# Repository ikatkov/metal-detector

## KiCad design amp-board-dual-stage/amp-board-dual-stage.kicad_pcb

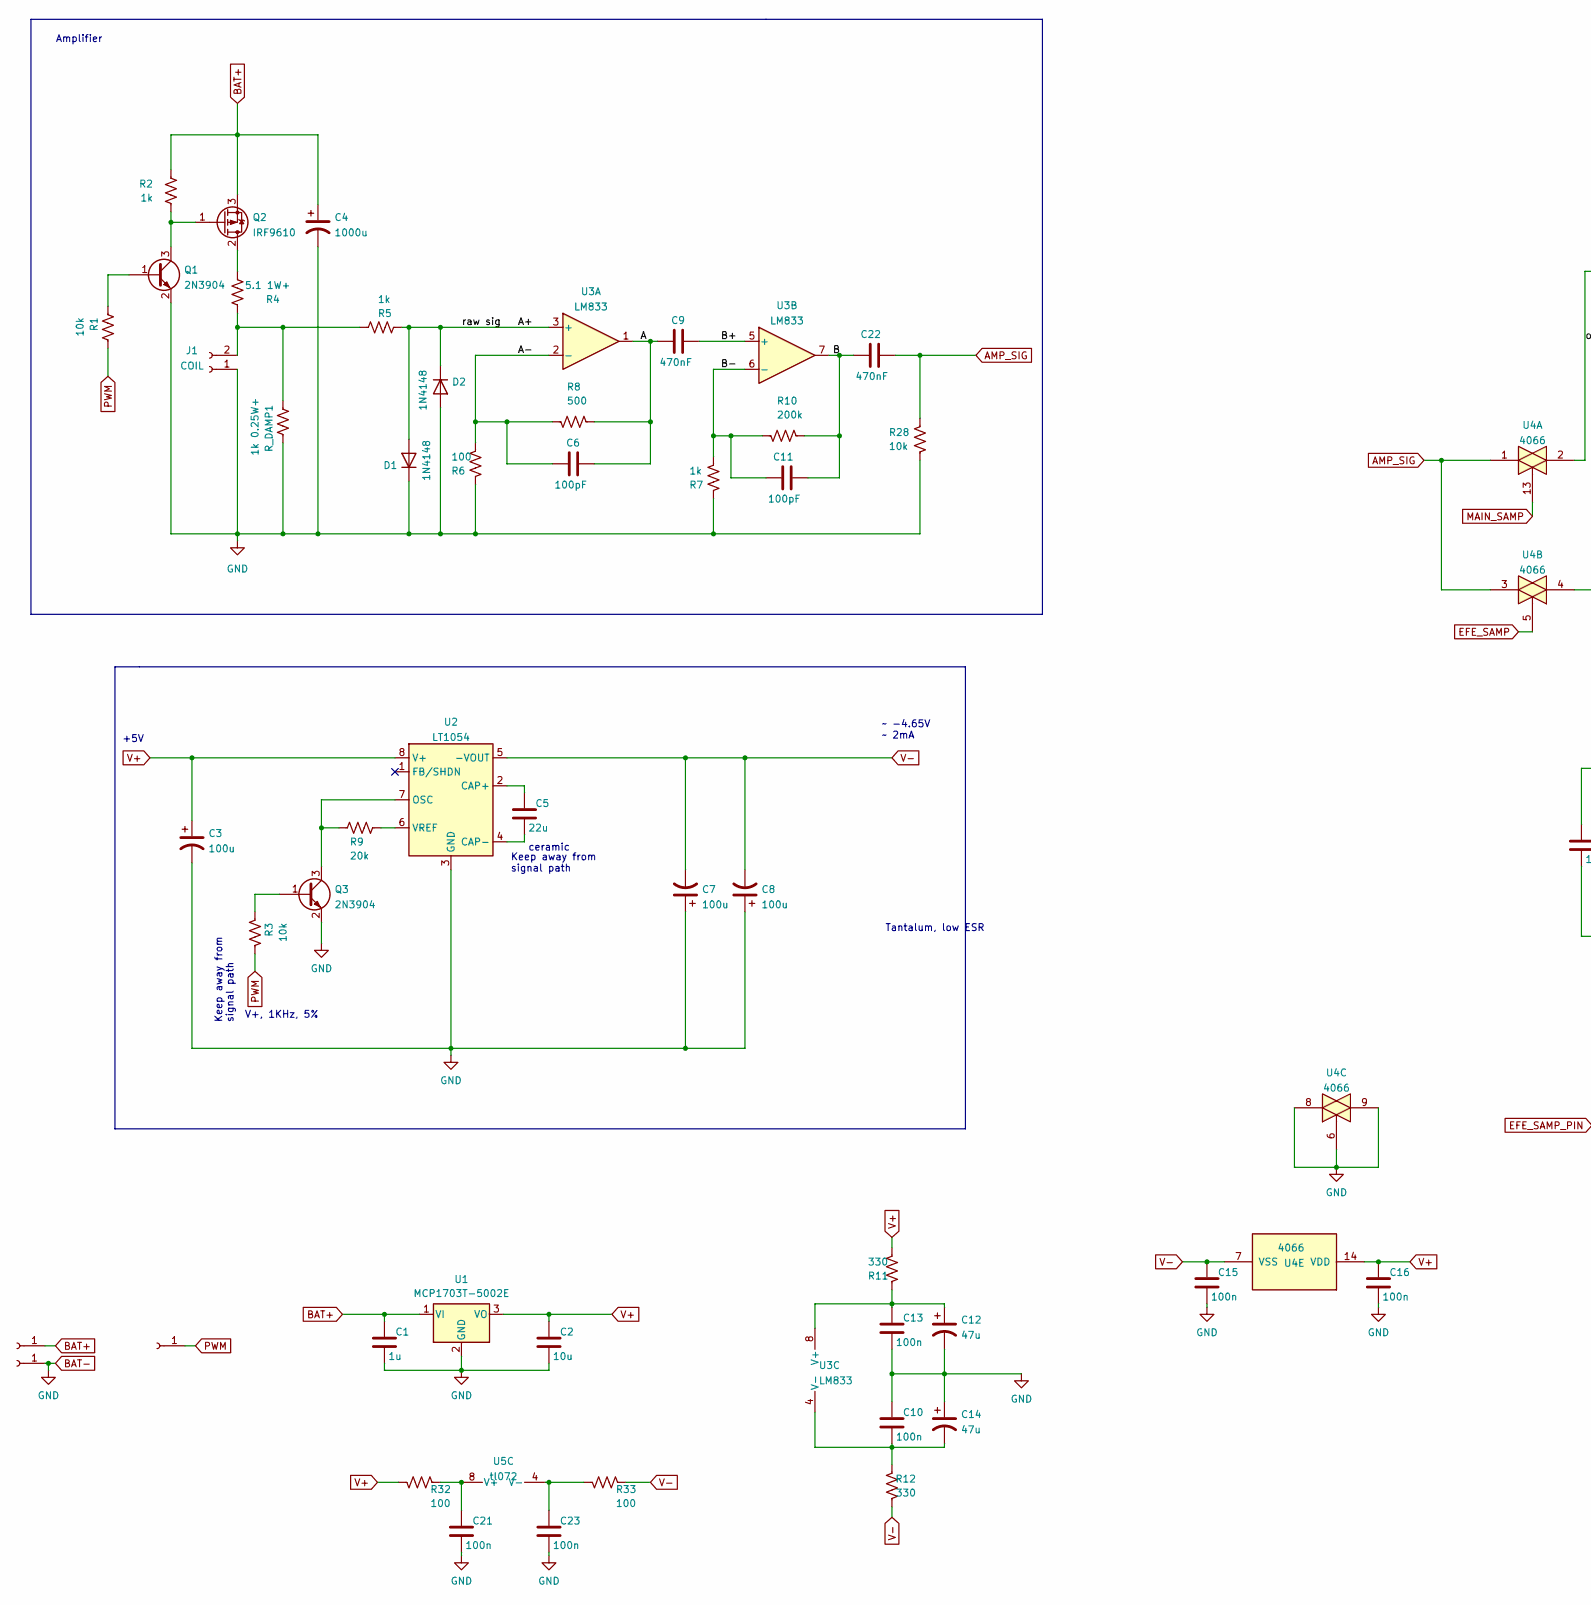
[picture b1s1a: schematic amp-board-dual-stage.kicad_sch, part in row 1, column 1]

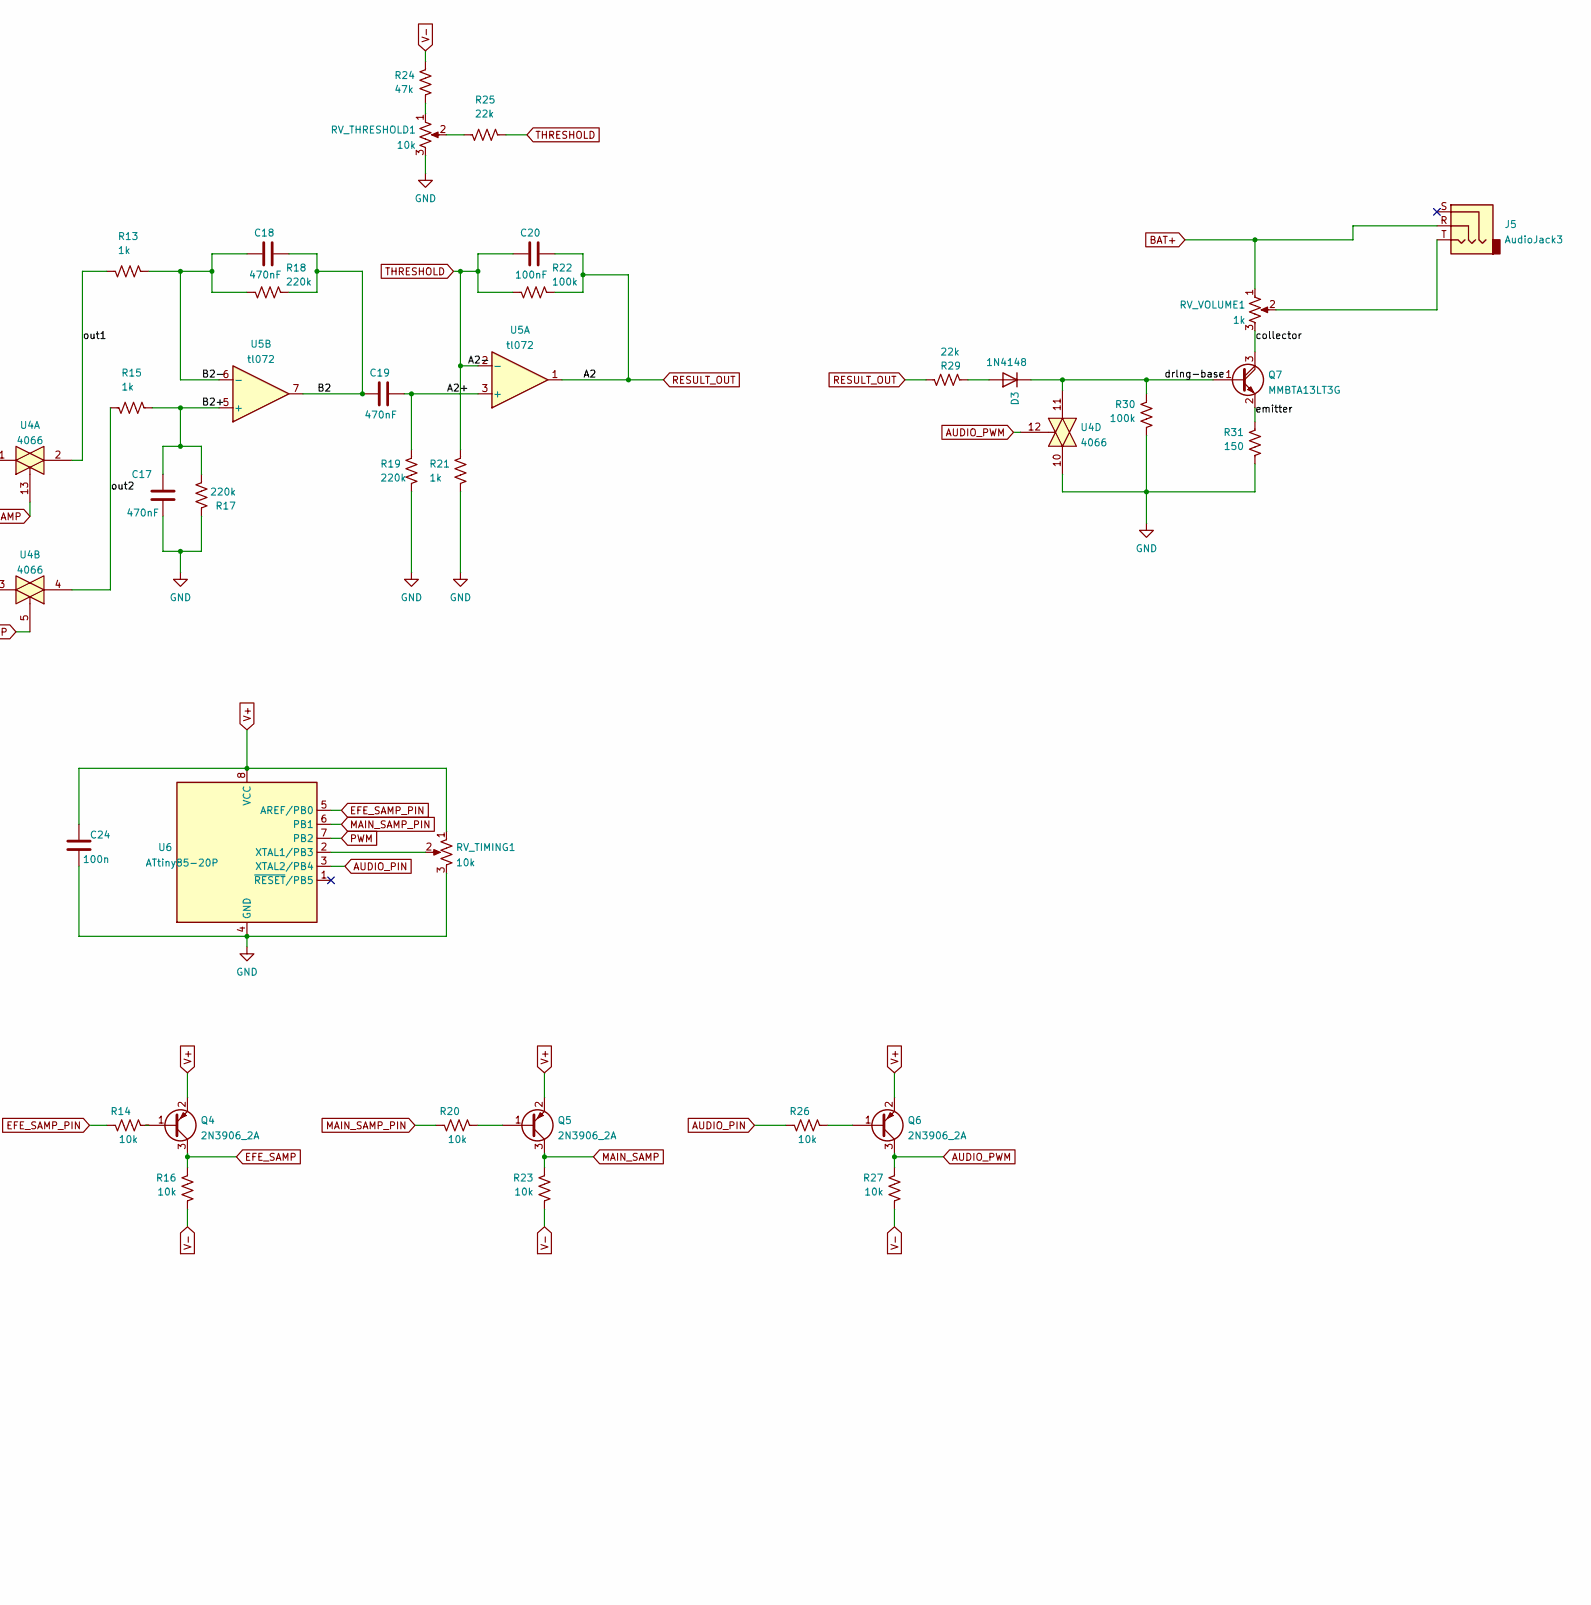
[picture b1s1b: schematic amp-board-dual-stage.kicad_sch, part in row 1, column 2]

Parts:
C1: 1u; C_1206_3216Metric
C2: 10u; C_1206_3216Metric
C3: 100u; CP_EIA-7361-438_AVX-U_Pad2.18x3.30mm_HandSolder
C4: 1000u; CP_Radial_D10.0mm_P5.00mm
C5: 22u; C_1206_3216Metric
C6, C11: 100pF; C_1206_3216Metric
C7, C8: 100u; CP_Radial_D5.0mm_P2.50mm
C9, C17, C18, C19, C22: 470nF; C_1206_3216Metric
C10, C13, C15, C16, C21, C23, C24: 100n; C_1206_3216Metric
C12, C14: 47u; CP_EIA-3528-21_Kemet-B_Pad1.50x2.35mm_HandSolder
C20: 100nF; C_1206_3216Metric
D1, D2, D3: 1N4148; D_1206_3216Metric
J1: COIL; TerminalBlock_Phoenix_MKDS-1,5-2-5.08_1x02_P5.08mm_Horizont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
J2: BAT+; SolderWirePad_1x01_SMD_2x4mm
J3: BAT-; SolderWirePad_1x01_SMD_2x4mm
J4: PWM; SolderWirePad_1x01_SMD_2x4mm
J5: AudioJack3; audio-jack
Q1, Q3: 2N3904; SOT-23
Q2: IRF9610; TO-220-3_Vertical
Q4, Q5, Q6: 2N3906_2A; SOT-23
Q7: MMBTA13LT3G; SOT-23
R1, R3, R14, R16, R20, R23, R26, R27, R28: 10k; R_0805_2012Metric
R2, R7, R13, R15, R21: 1k; R_0805_2012Metric
R4: 5.1 1W+; R_Axial_DIN0411_L9.9mm_D3.6mm_P12.70mm_Horizontal
R5: 1k; R_1206_3216Metric_Pad1.30x1.75mm_HandSolder
R6, R32, R33: 100; R_0805_2012Metric
R8: 500; R_0805_2012Metric
R9: 20k; R_0805_2012Metric
R10: 200k; R_0805_2012Metric
R11: 330; R_0805_2012Metric
R12: 330; R_1206_3216Metric_Pad1.30x1.75mm_HandSolder
R17, R18, R19: 220k; R_0805_2012Metric
R22, R30: 100k; R_0805_2012Metric
R24: 47k; R_0805_2012Metric
R25: 22k; R_1206_3216Metric_Pad1.30x1.75mm_HandSolder
R29: 22k; R_0805_2012Metric
R31: 150; R_0805_2012Metric
RV_THRESHOLD1: 10k; JST_EH_B3B-EH-A_1x03_P2.50mm_Vertical
RV_TIMING1: 10k; JST_EH_B3B-EH-A_1x03_P2.50mm_Vertical
RV_VOLUME1: 1k; JST_EH_B3B-EH-A_1x03_P2.50mm_Vertical
R_DAMP1: 1k 0.25W+; R_Axial_DIN0207_L6.3mm_D2.5mm_P10.16mm_Horizontal
U1: MCP1703T-5002E; SOT-223-3_TabPin2
U2: LT1054; SOIC-8_3.9x4.9mm_P1.27mm
U3: LM833; SOIC-8_3.9x4.9mm_P1.27mm
U4: 4066; SO-14_3.9x8.65mm_P1.27mm
U5: tl072; SOIC-8_3.9x4.9mm_P1.27mm
U6: ATtiny85-20P; DIP-8_W7.62mm

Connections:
/A: C6.2, C9.1, R8.1, U3.1
/A2+: C19.2, R19.2, U5.3 (+)
/A+: D1.2 (A), D2.1 (K), R5.1, U3.3 (+)
/A-: C6.1, R6.2, R8.2, U3.2 (-)
/B: C11.2, C22.1, R10.1, U3.7
/B2: C18.2, C19.1, R18.1, U5.7
/B2+: C17.2, R15.1, R17.1, U5.5 (+)
/B2-: C18.1, R13.1, R18.2, U5.6 (-)
/B+: C9.2, U3.5 (+)
/B-: C11.1, R7.2, R10.2, U3.6 (-)
/collector: Q7.3 (C), RV_VOLUME1.3
/drlng-base: D3.1 (K), Q7.1 (B), R30.1, U4.11
/emitter: Q7.2 (E), R31.1
/out1: R13.2, U4.2
/out2: R15.2, U4.4
AMP_SIG: C22.2, R28.2, U4.1, U4.3
AUDIO_PIN: R26.1, U6.3 (XTAL2/PB4)
AUDIO_PWM: Q6.3 (C), R27.1, U4.12
BAT+: C1.1, C4.1, J2.1, J5.R, Q2.3 (S), R2.2, RV_VOLUME1.1, U1.1 (VI)
BAT-: C1.2, C2.2, C3.2, C4.2, C7.1, C8.1, C10.1, C12.2, C13.2, C14.1, C15.2, C16.2, C17.1, C21.2, C23.2, C24.2, D1.1 (K), D2.2 (A), J1.1, J3.1, Q1.2 (E), Q3.2 (E), R6.1, R7.1, R17.2, R19.1, R21.1, R28.1, R30.2, R31.2, RV_THRESHOLD1.3, RV_TIMING1.3, R_DAMP1.1, U1.2 (GND), U2.3 (GND), U4.6, U4.8, U4.9, U4.10, U6.4 (GND)
EFE_SAMP: Q4.3 (C), R16.1, U4.5
EFE_SAMP_PIN: R14.1, U6.5 (AREF/PB0)
MAIN_SAMP: Q5.3 (C), R23.1, U4.13
MAIN_SAMP_PIN: R20.1, U6.6 (PB1)
unnamed: C5.1, U2.2 (CAP+)
unnamed: C5.2, U2.4 (CAP-)
unnamed: C10.2, C14.2, R12.1, U3.4 (V-)
unnamed: C12.1, C13.1, R11.1, U3.8 (V+)
unnamed: D3.2 (A), R29.1
unnamed: J1.2, R4.2, R5.2, R_DAMP1.2
unnamed: J5.T, RV_VOLUME1.2
unnamed: Q1.1 (B), R1.2
unnamed: Q1.3 (C), Q2.1 (G), R2.1
unnamed: Q2.2 (D), R4.1
unnamed: Q3.1 (B), R3.2
unnamed: Q3.3 (C), R9.2, U2.7 (OSC)
unnamed: Q4.1 (B), R14.2
unnamed: Q5.1 (B), R20.2
unnamed: Q6.1 (B), R26.2
unnamed: R9.1, U2.6 (VREF)
unnamed: R24.1, RV_THRESHOLD1.1
unnamed: R25.2, RV_THRESHOLD1.2
unnamed: RV_TIMING1.2, U6.2 (XTAL1/PB3)
PWM: J4.1, R1.1, R3.1, U6.7 (PB2)
RESULT_OUT: C20.2, R22.1, R29.2, U5.1
THRESHOLD: C20.1, R21.2, R22.2, R25.1, U5.2 (-)

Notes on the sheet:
V+, 1KHz, 5%
Amplifier
Keep away from signal path
ceramic
Tantalum, low ESR
~ -4.65V ~ 2mA
+5V

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
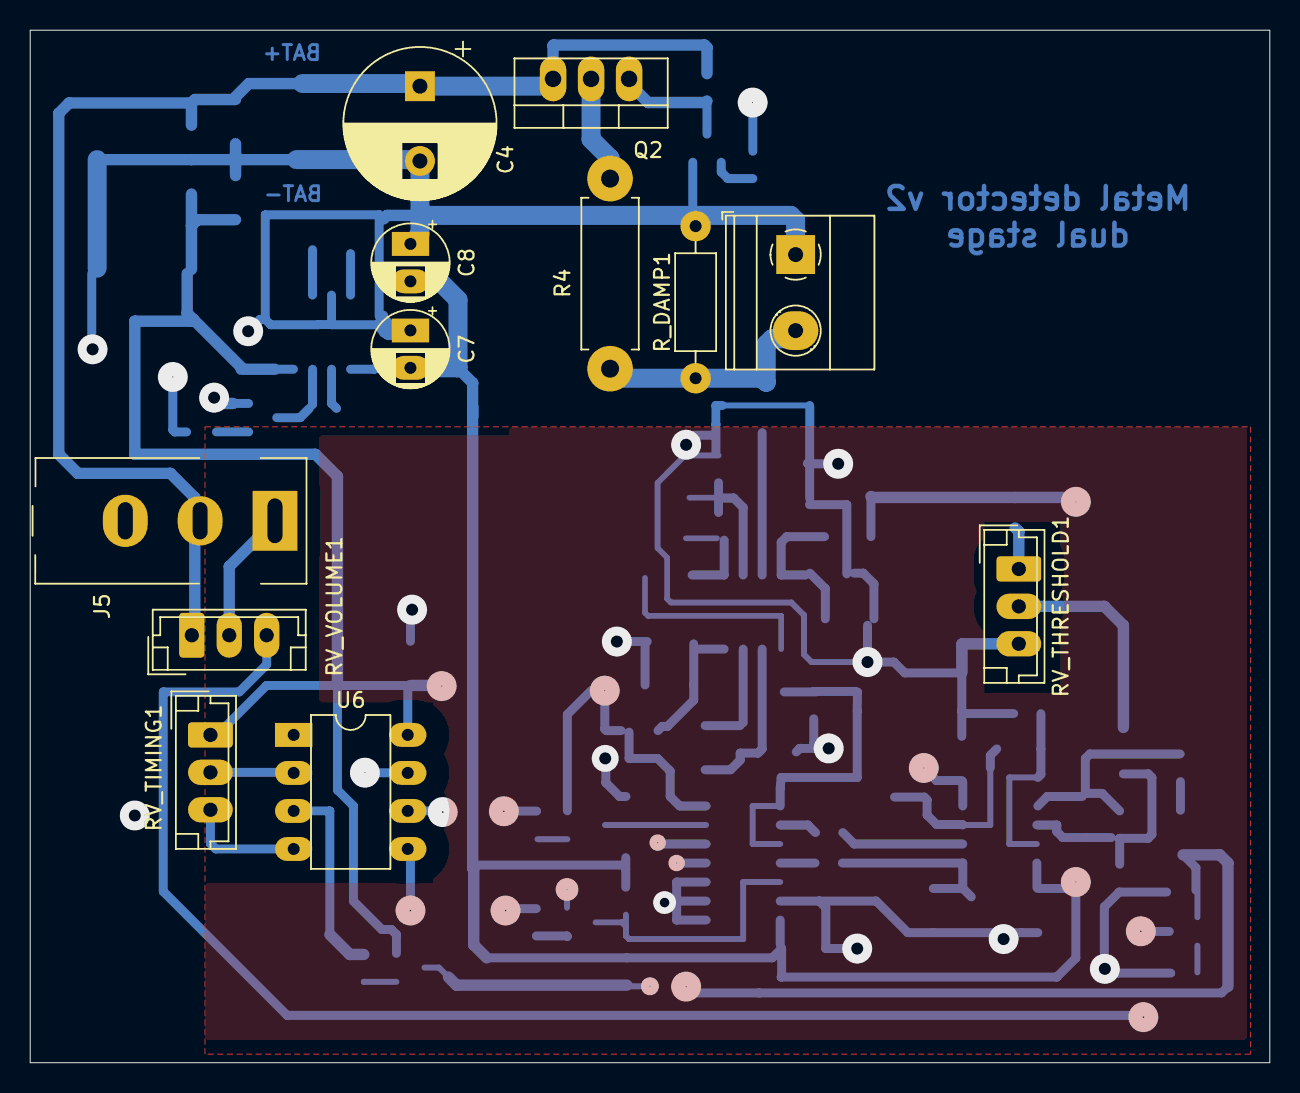
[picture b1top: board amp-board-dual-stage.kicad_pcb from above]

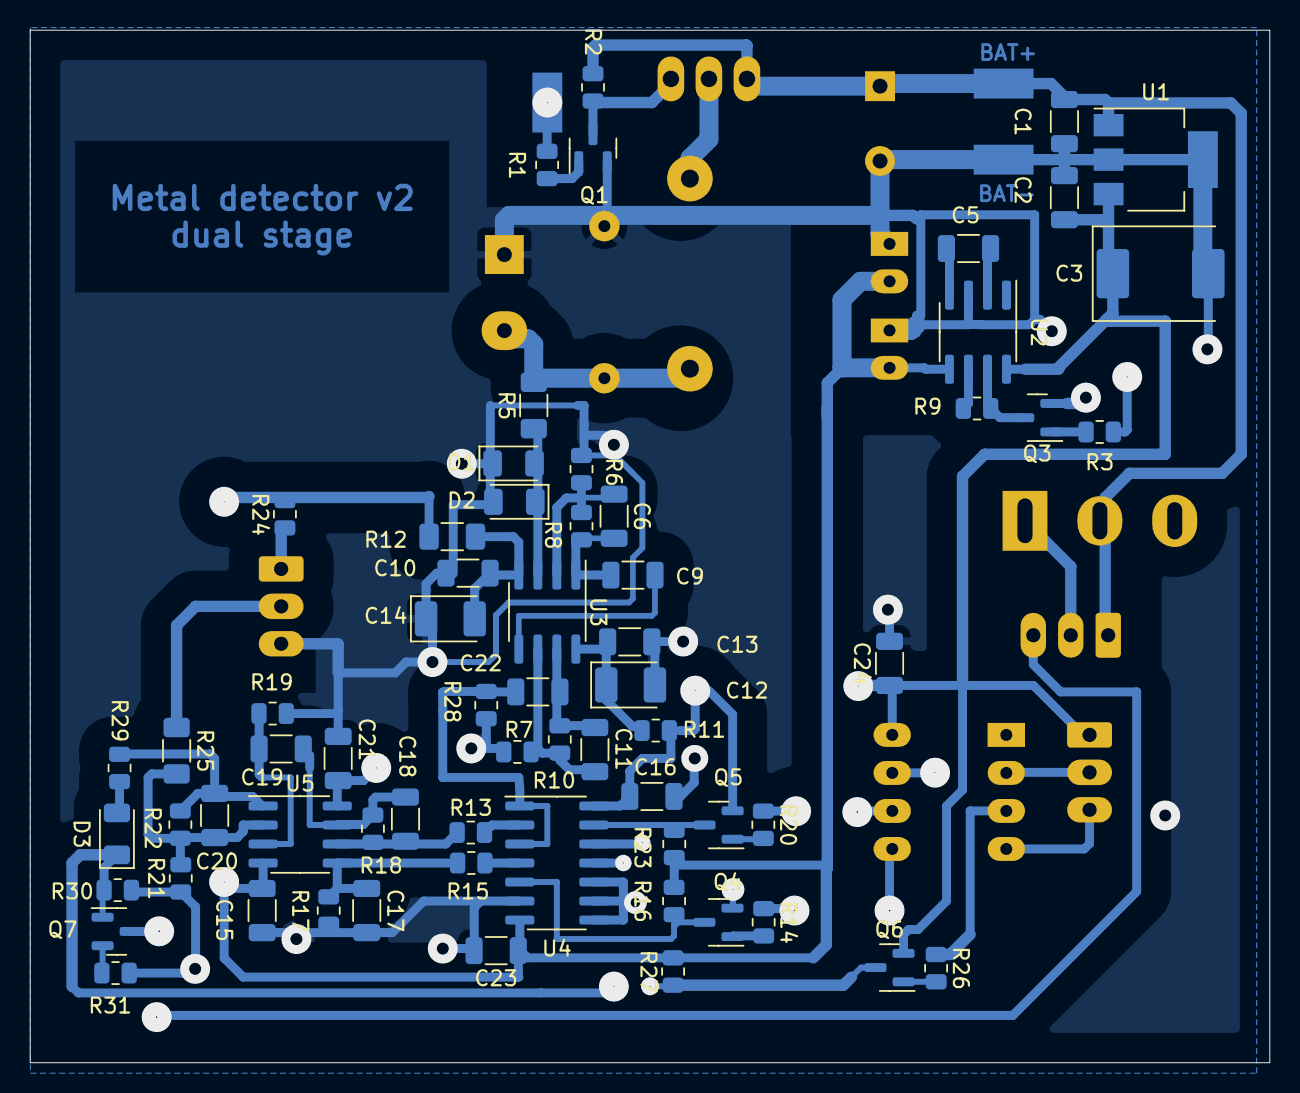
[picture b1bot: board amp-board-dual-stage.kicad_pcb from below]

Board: 4 copper layers, 82.8 x 69.0 mm, 80 parts (68 on the bottom side), 48 nets.

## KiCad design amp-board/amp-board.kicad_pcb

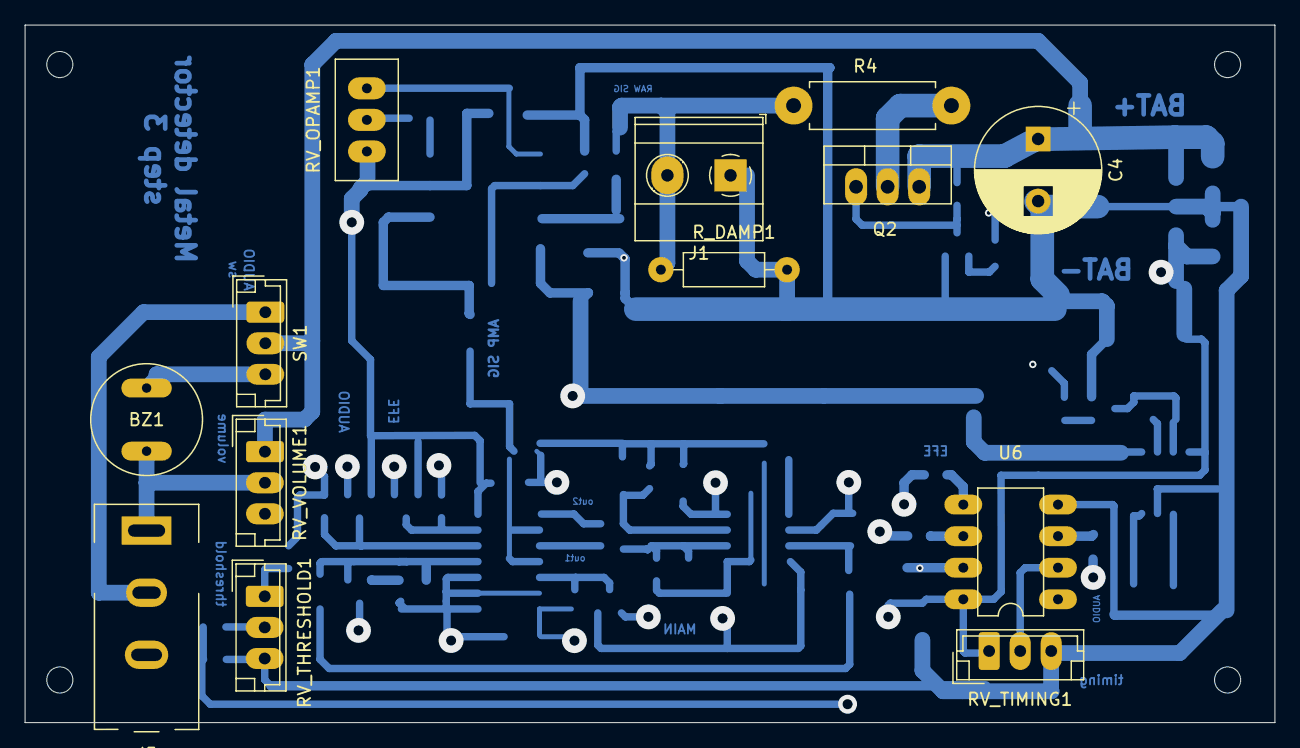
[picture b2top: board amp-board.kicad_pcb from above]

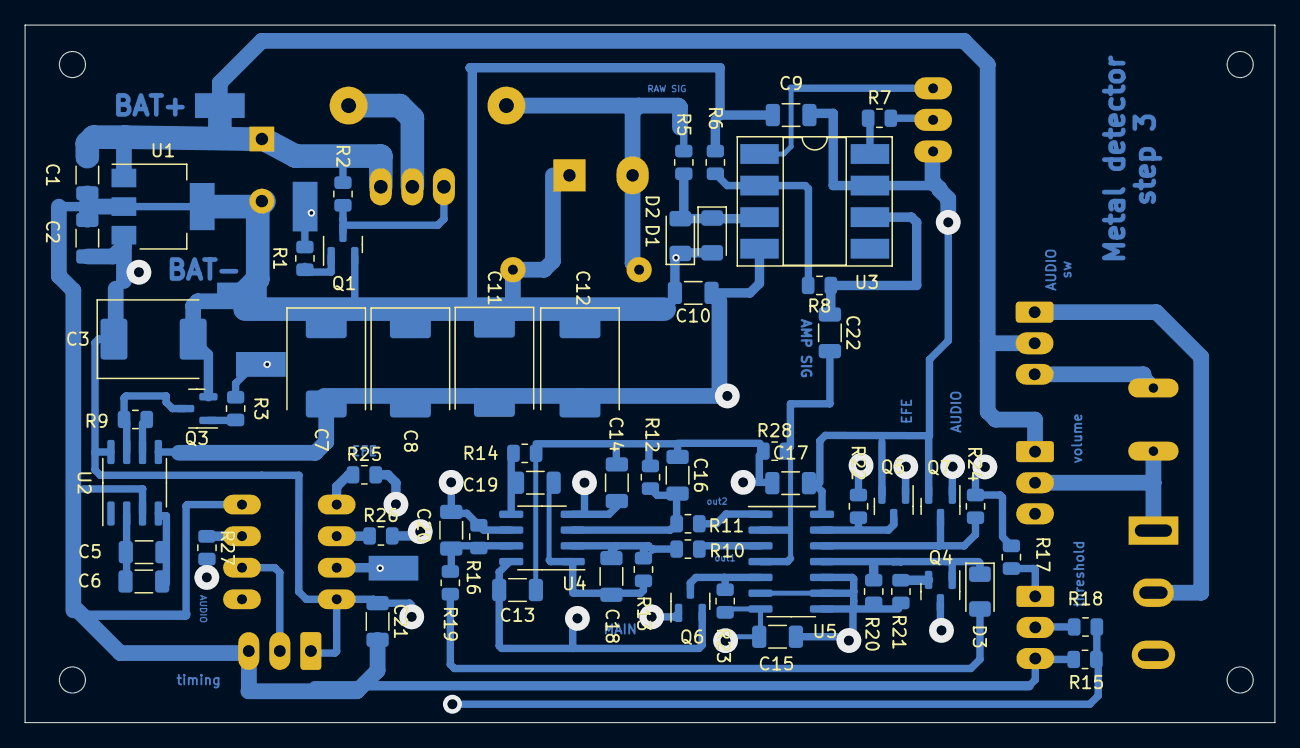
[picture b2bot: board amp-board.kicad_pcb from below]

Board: 4 copper layers, 100.6 x 56.1 mm, 78 parts (65 on the bottom side), 48 nets.

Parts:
BZ1: Buzzer; Buzzer-GT-0905A
C1: 1u; C_1206_3216Metric
C2: 10u; C_1206_3216Metric
C3, C7, C8, C11, C12: 100u; CP_EIA-7361-438_AVX-U_Pad2.18x3.30mm_HandSolder
C4: 1000u; CP_Radial_D10.0mm_P5.00mm
C5, C6: 22u; C_1206_3216Metric
C9, C10, C13, C14, C15, C17, C21: 100n; C_1206_3216Metric
C16, C18, C19, C22: 470nF; C_1206_3216Metric
C20: 100nF; C_1206_3216Metric
D1, D2, D3: 1N4148; D_1206_3216Metric
J1: COIL; TerminalBlock_Phoenix_MKDS-1,5-2-5.08_1x02_P5.08mm_Horizont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
J2: BAT+; SolderWirePad_1x01_SMD_2x4mm
J3: BAT-; SolderWirePad_1x01_SMD_2x4mm
J4: PWM; SolderWirePad_1x01_SMD_2x4mm
J5: AudioJack3; audio-jack
Q1, Q3: 2N3904; SOT-23
Q2: IRF9610; TO-220-3_Vertical
Q4: MMBTA13LT3G; SOT-23
Q5, Q6, Q7: 2N3906_2A; SOT-23
R1, R3, R22, R23, R24, R25, R26, R27: 10k; R_0805_2012Metric
R2, R5, R6, R10, R11, R15, R28: 1k; R_0805_2012Metric
R4: 5.1 1W+; R_Axial_DIN0411_L9.9mm_D3.6mm_P12.70mm_Horizontal
R7, R18, R19: 22k; R_0805_2012Metric
R8: 1M; R_0805_2012Metric
R9: 20k; R_0805_2012Metric
R12, R13, R14: 220k; R_0805_2012Metric
R16, R20: 100k; R_0805_2012Metric
R17: 47k; R_0805_2012Metric
R21: 150; R_0805_2012Metric
RV_OPAMP1: 100k; Potentiometer_Bourns_3296W_Vertical
RV_THRESHOLD1: 10k; JST_EH_B3B-EH-A_1x03_P2.50mm_Vertical
RV_TIMING1: 10k; JST_EH_B3B-EH-A_1x03_P2.50mm_Vertical
RV_VOLUME1: 1k; JST_EH_B3B-EH-A_1x03_P2.50mm_Vertical
R_DAMP1: 1k 0.25W+; R_Axial_DIN0207_L6.3mm_D2.5mm_P10.16mm_Horizontal
SW1: SW_SPDT; JST_EH_B3B-EH-A_1x03_P2.50mm_Vertical
U1: MCP1703T-5002E; SOT-223-3_TabPin2
U2: LT1054; SOIC-8_3.9x4.9mm_P1.27mm
U3: NE5534; DIP-8_W8.89mm_SMDSocket_LongPads
U4: LM358; SOIC-8_3.9x4.9mm_P1.27mm
U5: 4066; SO-14_3.9x8.65mm_P1.27mm
U6: ATtiny85-20P; DIP-8_W7.62mm

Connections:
/collector: Q4.3 (C), RV_VOLUME1.3
/drlng-base: D3.1 (K), Q4.1 (B), R20.1, U5.11
/emitter: Q4.2 (E), R21.1
/out1: R10.2, U5.3
/out2: R11.2, U5.1
/raw sig: D1.2 (A), D2.1 (K), R5.1, U3.3 (+)
/stg1: C18.2, C19.1, R13.1, U4.1
AMP_SIG: C22.2, R28.2, U5.2, U5.4
AUDIO_PIN: R27.1, U6.3 (XTAL2/PB4)
AUDIO_PWM: Q7.3 (C), R24.1, U5.12
BAT+: C1.1, C4.1, J2.1, Q2.3 (S), R2.2, RV_VOLUME1.1, SW1.2 (B), U1.1 (VI)
BAT-: C1.2, C2.2, C3.2, C4.2, C7.1, C8.1, C9.2, C10.2, C11.1, C12.1, C13.2, C14.2, C15.2, C16.1, C17.2, C21.2, D1.1 (K), D2.2 (A), J1.1, J3.1, Q1.2 (E), Q3.2 (E), R6.1, R12.2, R14.1, R15.1, R20.2, R21.2, R28.1, RV_THRESHOLD1.3, RV_TIMING1.3, R_DAMP1.1, U1.2 (GND), U2.3 (GND), U5.6, U5.8, U5.9, U5.10, U6.4 (GND)
EFE_SAMP: Q5.3 (C), R22.1, U5.13
EFE_SAMP_PIN: R25.1, U6.5 (AREF/PB0)
MAIN_SAMP: Q6.3 (C), R23.1, U5.5
MAIN_SAMP_PIN: R26.1, U6.6 (PB1)
unnamed: BZ1.1 (-), SW1.3 (C)
unnamed: BZ1.2 (+), J5.T, RV_VOLUME1.2
unnamed: C5.1, C6.1, U2.2 (CAP+)
unnamed: C5.2, C6.2, U2.4 (CAP-)
unnamed: C16.2, R11.1, R12.1, U4.3 (+)
unnamed: C18.1, R10.1, R13.2, U4.2 (-)
unnamed: C19.2, R14.2, U4.5 (+)
unnamed: D3.2 (A), R19.1
unnamed: J1.2, R4.2, R5.2, R_DAMP1.2
unnamed: J5.R, SW1.1 (A)
unnamed: Q1.1 (B), R1.2
unnamed: Q1.3 (C), Q2.1 (G), R2.1
unnamed: Q2.2 (D), R4.1
unnamed: Q3.1 (B), R3.2
unnamed: Q3.3 (C), R9.2, U2.7 (OSC)
unnamed: Q5.1 (B), R25.2
unnamed: Q6.1 (B), R26.2
unnamed: Q7.1 (B), R27.2
unnamed: R6.2, R8.2, U3.2 (-)
unnamed: R7.1, U3.8 (C/B)
unnamed: R7.2, RV_OPAMP1.2
unnamed: C22.1, R8.1, U3.6
unnamed: R9.1, U2.6 (VREF)
unnamed: R17.1, RV_THRESHOLD1.1
unnamed: R18.2, RV_THRESHOLD1.2
unnamed: RV_OPAMP1.3, U3.1 (BAL)
unnamed: RV_TIMING1.2, U6.2 (XTAL1/PB3)
PWM: J4.1, R1.1, R3.1, U6.7 (PB2)
RESULT_OUT: C20.2, R16.1, R19.2, U4.7
THRESHOLD: C20.1, R15.2, R16.2, R18.1, U4.6 (-)
V+: C2.1, C3.1, C9.1, C13.1, C17.1, C21.1, Q5.2 (E), Q6.2 (E), Q7.2 (E), RV_OPAMP1.1, RV_TIMING1.1, U1.3 (VO), U2.8 (V+), U3.7 (V+), U4.8 (V+), U5.14 (VDD), U6.8 (VCC)
V-: C7.2, C8.2, C10.1, C11.2, C12.2, C14.1, C15.1, R17.2, R22.2, R23.2, R24.2, U2.5 (-VOUT), U3.4 (V-), U4.4 (V-), U5.7 (VSS)

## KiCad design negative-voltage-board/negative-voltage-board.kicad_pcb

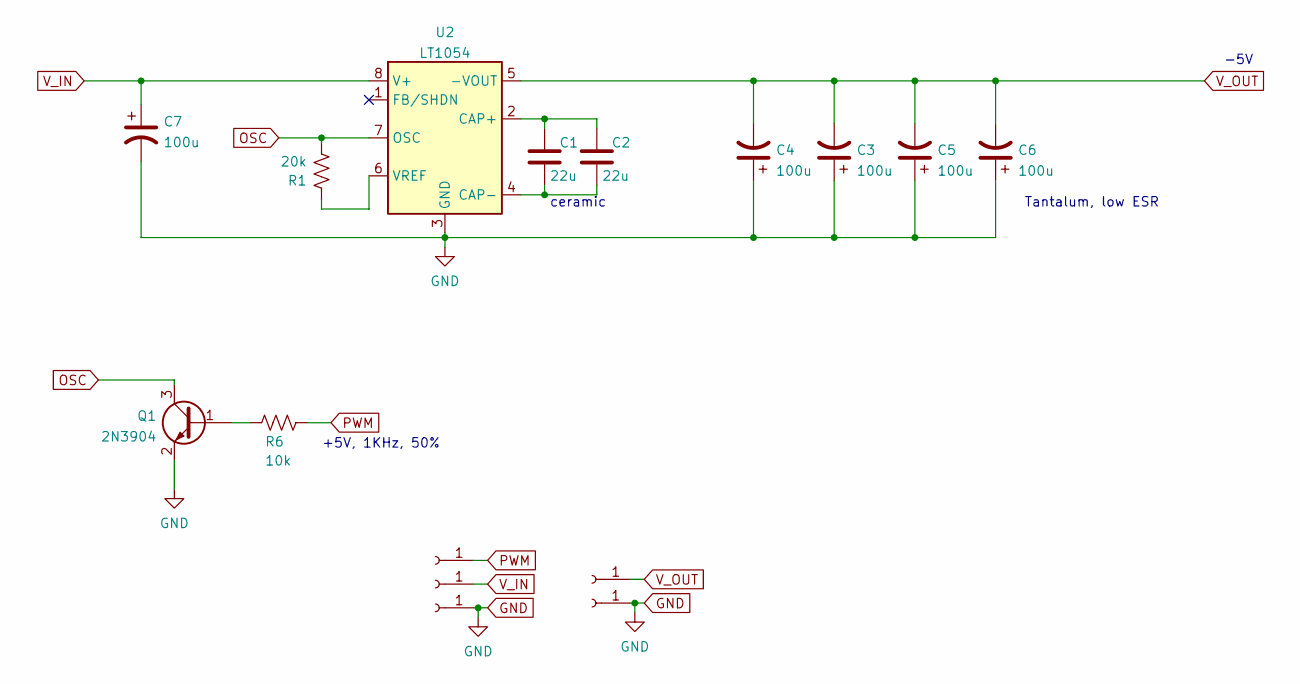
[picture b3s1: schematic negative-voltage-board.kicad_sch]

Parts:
C1, C2: 22u; C_1206_3216Metric
C3, C4, C5, C6, C7: 100u; CP_EIA-7361-438_AVX-U_Pad2.18x3.30mm_HandSolder
J1: Vin; PinSocket_1x01_P2.54mm_Vertical
J2, J4: GND; PinSocket_1x01_P2.54mm_Vertical
J3: Vout; PinSocket_1x01_P2.54mm_Vertical
J5: PWM; PinSocket_1x01_P2.54mm_Vertical
Q1: 2N3904; SOT-23
R1: 20k; R_0805_2012Metric
R6: 10k; R_0805_2012Metric
U2: LT1054; DIP-8_W8.89mm_SMDSocket_LongPads

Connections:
GND: C3.1, C4.1, C5.1, C6.1, C7.2, J2.1, J4.1, Q1.2 (E), U2.3 (GND)
unnamed: C1.1, C2.1, U2.2 (CAP+)
unnamed: C1.2, C2.2, U2.4 (CAP-)
unnamed: Q1.1 (B), R6.2
unnamed: R1.1, U2.6 (VREF)
OSC: Q1.3 (C), R1.2, U2.7 (OSC)
PWM: J5.1, R6.1
V_IN: C7.1, J1.1, U2.8 (V+)
V_OUT: C3.2, C4.2, C5.2, C6.2, J3.1, U2.5 (-VOUT)

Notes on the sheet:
ceramic
Tantalum, low ESR
-5V
+5V, 1KHz, 50%

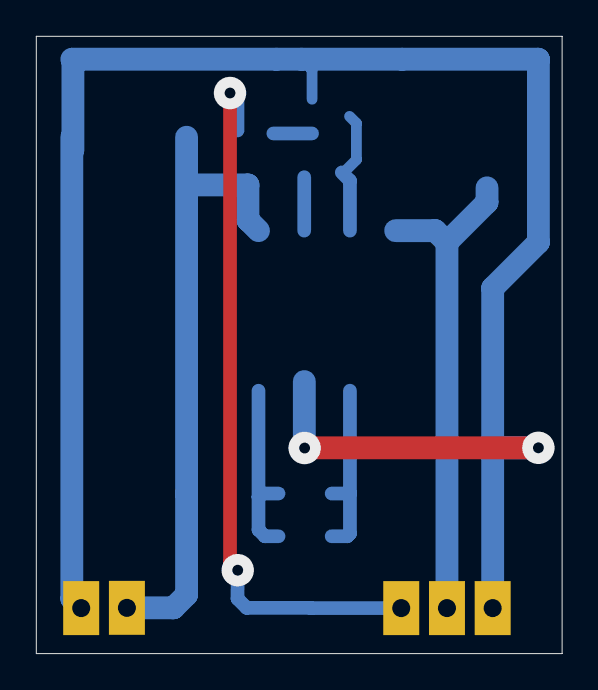
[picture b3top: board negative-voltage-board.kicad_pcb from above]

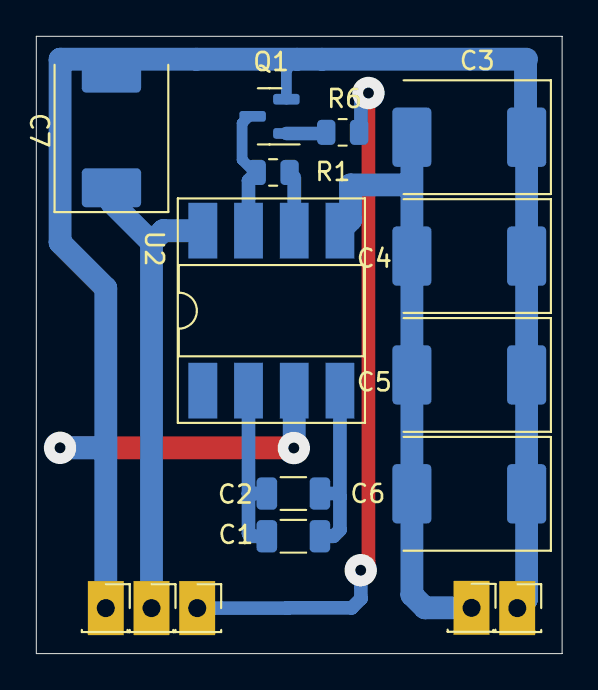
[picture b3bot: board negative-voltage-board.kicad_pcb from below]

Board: 4 copper layers, 29.2 x 34.3 mm, 16 parts (16 on the bottom side), 9 nets.

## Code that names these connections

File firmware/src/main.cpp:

// Fuses needs to be set to
// lfuse f1 - 16Mhz internal clock, no Divide clock by 8 internally
// hfuse df - default
// avrdude -p attiny85  -b 19200 -cusbtiny -U lfuse:w:0xf1:m
// avrdude -p attiny85  -b 19200 -cusbtiny -U hfuse:w:0xdf:m
#include "Arduino.h"

;                         // RESET is Attiny85 pin4
#define delayPin A3       // Attiny85 pin2
#define audioPin PB4      // Attiny85 pin3
;                         // GND is Attiny85 pin4
#define efeSamplePin PB0  // Attiny85 pin5
#define mainSamplePin PB1 // Attiny85 pin6
#define txPin PB2         // Attiny85 pin7
;                         // VCC is Attiny85 pin8

// Default Detector Timings, has to be multiple of 4us
#define txPulseMicros 52       // Main pulse width
#define mainDelayMicros 6     // Main sample pulse delay
#define mainSampleMicros 52    // Main sample pulse width
#define efeDelayMicros 300     // EFE sample pulse delay
#define efeSampleMicros 52     // EFE sample pulse width
#define txCycleMicros 1020     // total cycle width 1ms
#define readDelayLimit 100     // Wait 100 cycle periods (100ms) before reading delay pot
#define MICROS_PER_INTERRUPT 4 // 4us elapsed per each interrupt call

uint8_t intState;
uint8_t readDelayCounter = 0;
boolean readDelayPot = false;
uint8_t varMainDelayMicros = mainDelayMicros;

void setup()
{
    // chip specific adjustment to local oscilator
    OSCCAL = 75;

    pinMode(txPin, OUTPUT);         // Set TX pin to output mode
    pinMode(mainSamplePin, OUTPUT); // Set main sample pin to output mode
    pinMode(efeSamplePin, OUTPUT);  // Set EFE sample pin to output mode
    pinMode(delayPin, INPUT);

    // initialize the timer0
    cli();
    TCCR0A = (1 << WGM01);              // Put timer0 in CTC mode and clear other bits
    TCCR0B = (1 << CS01) | (1 << CS00); // Timer0 prescaling 64 and clearing other bits
    TIMSK |= (1 << OCIE0A);             // enable timer1 compare interrupt
    OCR0A = 0;                          // set the timer0 count  - Count 0 cycles before calling ISR interrupt i.e. each 64cycles i.e. 4us
    sei();
    pinMode(audioPin, OUTPUT);
    analogWrite(audioPin, 127); // Set audioPin with 50% duty cycle PWM
}

void loop()
{
}

// called every 4uS, 64CPU cycles in each 4us
ISR(TIM0_COMPA_vect)
{
    switch (intState)
    {
    case 0:
        OCR0A = txPulseMicros / MICROS_PER_INTERRUPT;
        PORTB |= (1 << txPin); // Turn on Mosfet
        intState++;
        break;
    case 1:
        OCR0A = varMainDelayMicros / MICROS_PER_INTERRUPT;
        PORTB &= ~(1 << txPin); // Turn off Mosfet
        intState++;
        break;
    case 2:
        OCR0A = mainSampleMicros / MICROS_PER_INTERRUPT;
        PORTB &= ~(1 << mainSamplePin); // Turn on mainSample
        intState++;
        break;
    case 3:
        OCR0A = (efeDelayMicros + varMainDelayMicros) / MICROS_PER_INTERRUPT;
        PORTB |= (1 << mainSamplePin); // Turn off mainSample
        intState++;
        break;
    case 4:
        OCR0A = efeSampleMicros / MICROS_PER_INTERRUPT;
        PORTB &= ~(1 << efeSamplePin); // Turn on efeSample
        intState++;
        break;
    case 5:
        // ~19us (magic number) were spent on this case() code block execution
        uint32_t total = txPulseMicros + varMainDelayMicros + mainSampleMicros + efeDelayMicros + efeSampleMicros + 19;
        OCR0A = (txCycleMicros - total) / MICROS_PER_INTERRUPT;
        PORTB |= (1 << efeSamplePin); // Turn off efeSample
        intState = 0;

        readDelayCounter++;
        if (readDelayCounter >= readDelayLimit)
        {
            // analogRead returns 0-1023 i.e. adds 0-200us
            varMainDelayMicros = mainDelayMicros + 2 * analogRead(delayPin) / 10;
            readDelayCounter = 0;
        }

        break;
    }
}

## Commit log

2023-04-22 Initial
2023-04-22 add license
2023-04-22 add main and amp boards
2023-04-26 step2 layout
2023-04-26 firmware
2023-04-26 simulation
2023-04-26 step2 live measurements
2023-04-27 working attiny85 code
2023-07-05 2023-07-05
